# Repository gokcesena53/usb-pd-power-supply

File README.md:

# gopo — Masaüstü Güç Kaynağı

USB-C PD beslemeli, ESP32-C6 tabanlı, TFT ekranlı ve döner enkoderli
masaüstü ayarlanabilir güç kaynağı. Şematik ve PCB tasarımı KiCad ile yapılmıştır.

Depo yapısı [Open Hardware Template](https://github.com/mfhepp/open_hardware_template)
şablonunu izler.

## Klasör yapısı

| Klasör | İçerik |
| --- | --- |
| `hardware/` | KiCad projesi (`gopo.kicad_pro`, `.kicad_sch`, `.kicad_pcb`, `.kicad_dru`) ve kütüphane tabloları (`fp-lib-table`, `sym-lib-table`) |
| `hardware/libraries/` | Projeye özel sembol (`.kicad_sym`), footprint (`.pretty`) ve 3D model (`.3dshapes`) kütüphaneleri |
| `hardware/datasheets/` | Kullanılan bileşenlerin veri sayfaları |
| `hardware/docs/` | Ham ERC/DRC raporları, netlist'ler, doğrulama betikleri ve anlık görüntüler |
| `hardware/gerber/` | Üretim çıktıları (Gerber, drill) |
| `hardware/images/` | Şematik/PCB görüntüleri (PNG, SVG) |
| `hardware/pdf/` | Blok blok şematik PDF çıktıları ve inceleme belgeleri |
| `design_decisions/` | Tasarım kararları, hesaplamalar ve inceleme notları (Markdown) |
| `3d_design/` | Kutu/mekanik tasarım dosyaları |
| `software/` | Firmware, firmware gereksinimleri (`FIRMWARE_GEREKSINIMLERI.md`) ve yardımcı betikler |
| `backlog/` | Yapılacaklar ([Backlog.md](https://github.com/MrLesk/Backlog.md)); `backlog board` veya `backlog browser` ile görüntülenir |
| `docs/` | GitHub Pages proje sayfası |
| `.claude/skills/` | KiCad şema üretimi için Claude Code skill'i ve araçları |

## Şema araçları

`.claude/skills/kicad-schematic/` altında şema üretimi ve temizliği için
bir Claude Code skill'i ve iki bağımsız betik bulunur:

```bash
SK=.claude/skills/kicad-schematic/scripts
cd hardware
python3 ../$SK/render.py gopo.kicad_sch --list
python3 ../$SK/render.py gopo.kicad_sch --page 10 --crop 255 26 410 128 -o /tmp/r
python3 ../$SK/verify.py gopo.kicad_sch --show PD_VOUT V_PRE
```

`render.py` şemayı PNG'ye çevirir ve mm cinsinden bir bölgeye yakınlaşır;
`verify.py` ERC çalıştırıp netlist'i bir referansla karşılaştırır.
Gereksinimler: `kicad-cli`, `poppler-utils` (pdftoppm, pdftotext), Python 3.

Yöntem [American-Embedded/kistack](https://github.com/American-Embedded/kistack)
schematic skill'ine dayanır (MIT); kopyası ve lisansı skill'in `references/`
klasöründedir.

## Revizyonlar

Aktif revizyon **REV_B**'dir; `hardware/` klasöründeki tasarım budur.
Üretilmiş olan REV_A tasarımı depodan çıkarılmıştır ve yalnızca git geçmişinde
bulunur (`git log --diff-filter=D -- "masaüstü güç kaynağı.kicad_pcb"`).

Değişiklik kaydı için `CHANGES.TXT` dosyasına bakınız.

## Tasarım kuralları ve PCB üretimi

Tasarım kuralları `hardware/gopo.kicad_dru` dosyasındadır. Üretime göndermeden önce
seçtiğiniz üreticinin yeteneklerine uyduğunu doğrulayın.

PCB ipek baskısına ve şematiğe **"Licensed under CERN OHL v.1.2"** metnini
eklemeyi unutmayın.

## Lisans

Donanım tasarımı CERN OHL v.1.2 altında, `software/` klasöründeki yazılım MIT
lisansı altında dağıtılmaktadır. Ayrıntılar için `LICENSE` ve
`cern_ohl_v_1_2.txt` dosyalarına bakınız.

> **Not:** `LICENSE` dosyasındaki `<TELİF HAKKI SAHİBİ>` alanı henüz
> doldurulmamıştır; yayımlamadan önce doldurun veya farklı bir lisans seçin.

## Sorumluluk reddi

BU TASARIM VE YAZILIM, AÇIK VEYA ZIMNİ HİÇBİR GARANTİ OLMAKSIZIN "OLDUĞU GİBİ"
SAĞLANMAKTADIR. YAZARLAR VEYA TELİF HAKKI SAHİPLERİ, TASARIMIN VEYA YAZILIMIN
KULLANIMINDAN DOĞAN HİÇBİR TALEP, ZARAR VEYA SORUMLULUKTAN SORUMLU TUTULAMAZ.

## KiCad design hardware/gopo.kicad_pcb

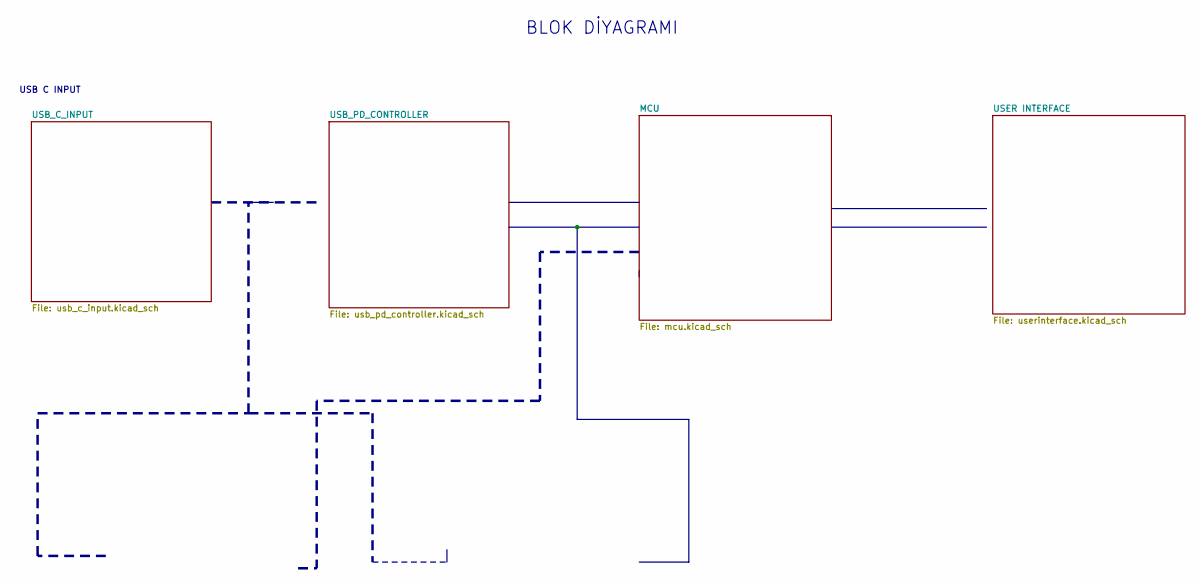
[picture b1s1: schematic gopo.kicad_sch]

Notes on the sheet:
USB C INPUT
BLOK DİYAGRAMI

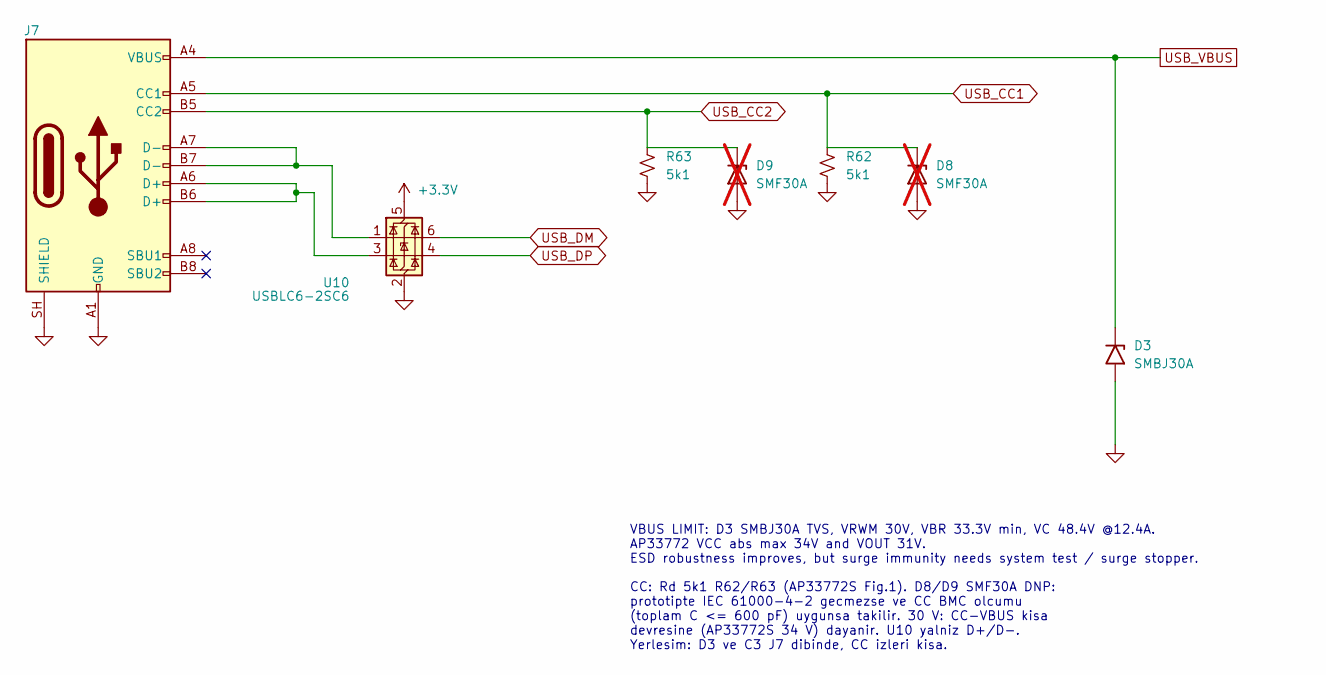
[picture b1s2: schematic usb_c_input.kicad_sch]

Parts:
D3: SMBJ30A; D_SMB; MPN SMBJ30A-E3/52
D8, D9: SMF30A; D_SOD-123F; MPN SMF30A-TKS; not fitted
J7: USB_C_Receptacle_USB2.0_16P; USB_C_Receptacle_GCT_USB4105-xx-A_16P_TopMnt_Horizontal; VoltageRating TBD; MPN USB4105-GF-A
R62, R63: 5k1; R_0402_1005Metric; Tolerance +/-1%; VoltageRating 50V; MPN HP02WAF5101TCE
U10: USBLC6-2SC6; SOT-23-6; MPN USBLC6-2SC6

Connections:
+3.3V: U10.5 (VBUS); also elsewhere on the board
GND: D3.2 (A2), D8.2 (A), D9.2 (A), J7.A1 (GND), J7.A12 (GND), J7.B1 (GND), J7.B12 (GND), J7.SH (SHIELD), R62.2, R63.2, U10.2 (GND); also elsewhere on the board
USB_CC1: D8.1 (K), J7.A5 (CC1), R62.1; also elsewhere on the board
USB_CC2: D9.1 (K), J7.B5 (CC2), R63.1; also elsewhere on the board
USB_VBUS: D3.1 (A1), J7.A4 (VBUS), J7.A9 (VBUS), J7.B4 (VBUS), J7.B9 (VBUS); also elsewhere on the board

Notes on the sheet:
VBUS LIMIT: D3 SMBJ30A TVS, VRWM 30V, VBR 33.3V min, VC 48.4V @12.4A. AP33772 VCC abs max 34V and VOUT 31V. ESD robustness improves, but surge immunity needs system test / surge stopper.
CC: Rd 5k1 R62/R63 (AP33772S Fig.1). D8/D9 SMF30A DNP: prototipte IEC 61000-4-2 gecmezse ve CC BMC olcumu (toplam C <= 600 pF) uygunsa takilir. 30 V: CC-VBUS kisa devresine (AP33772S 34 V) dayanir. U10 yalniz D+/D-. Yerlesim: D3 ve C3 J7 dibinde, CC izleri kisa.

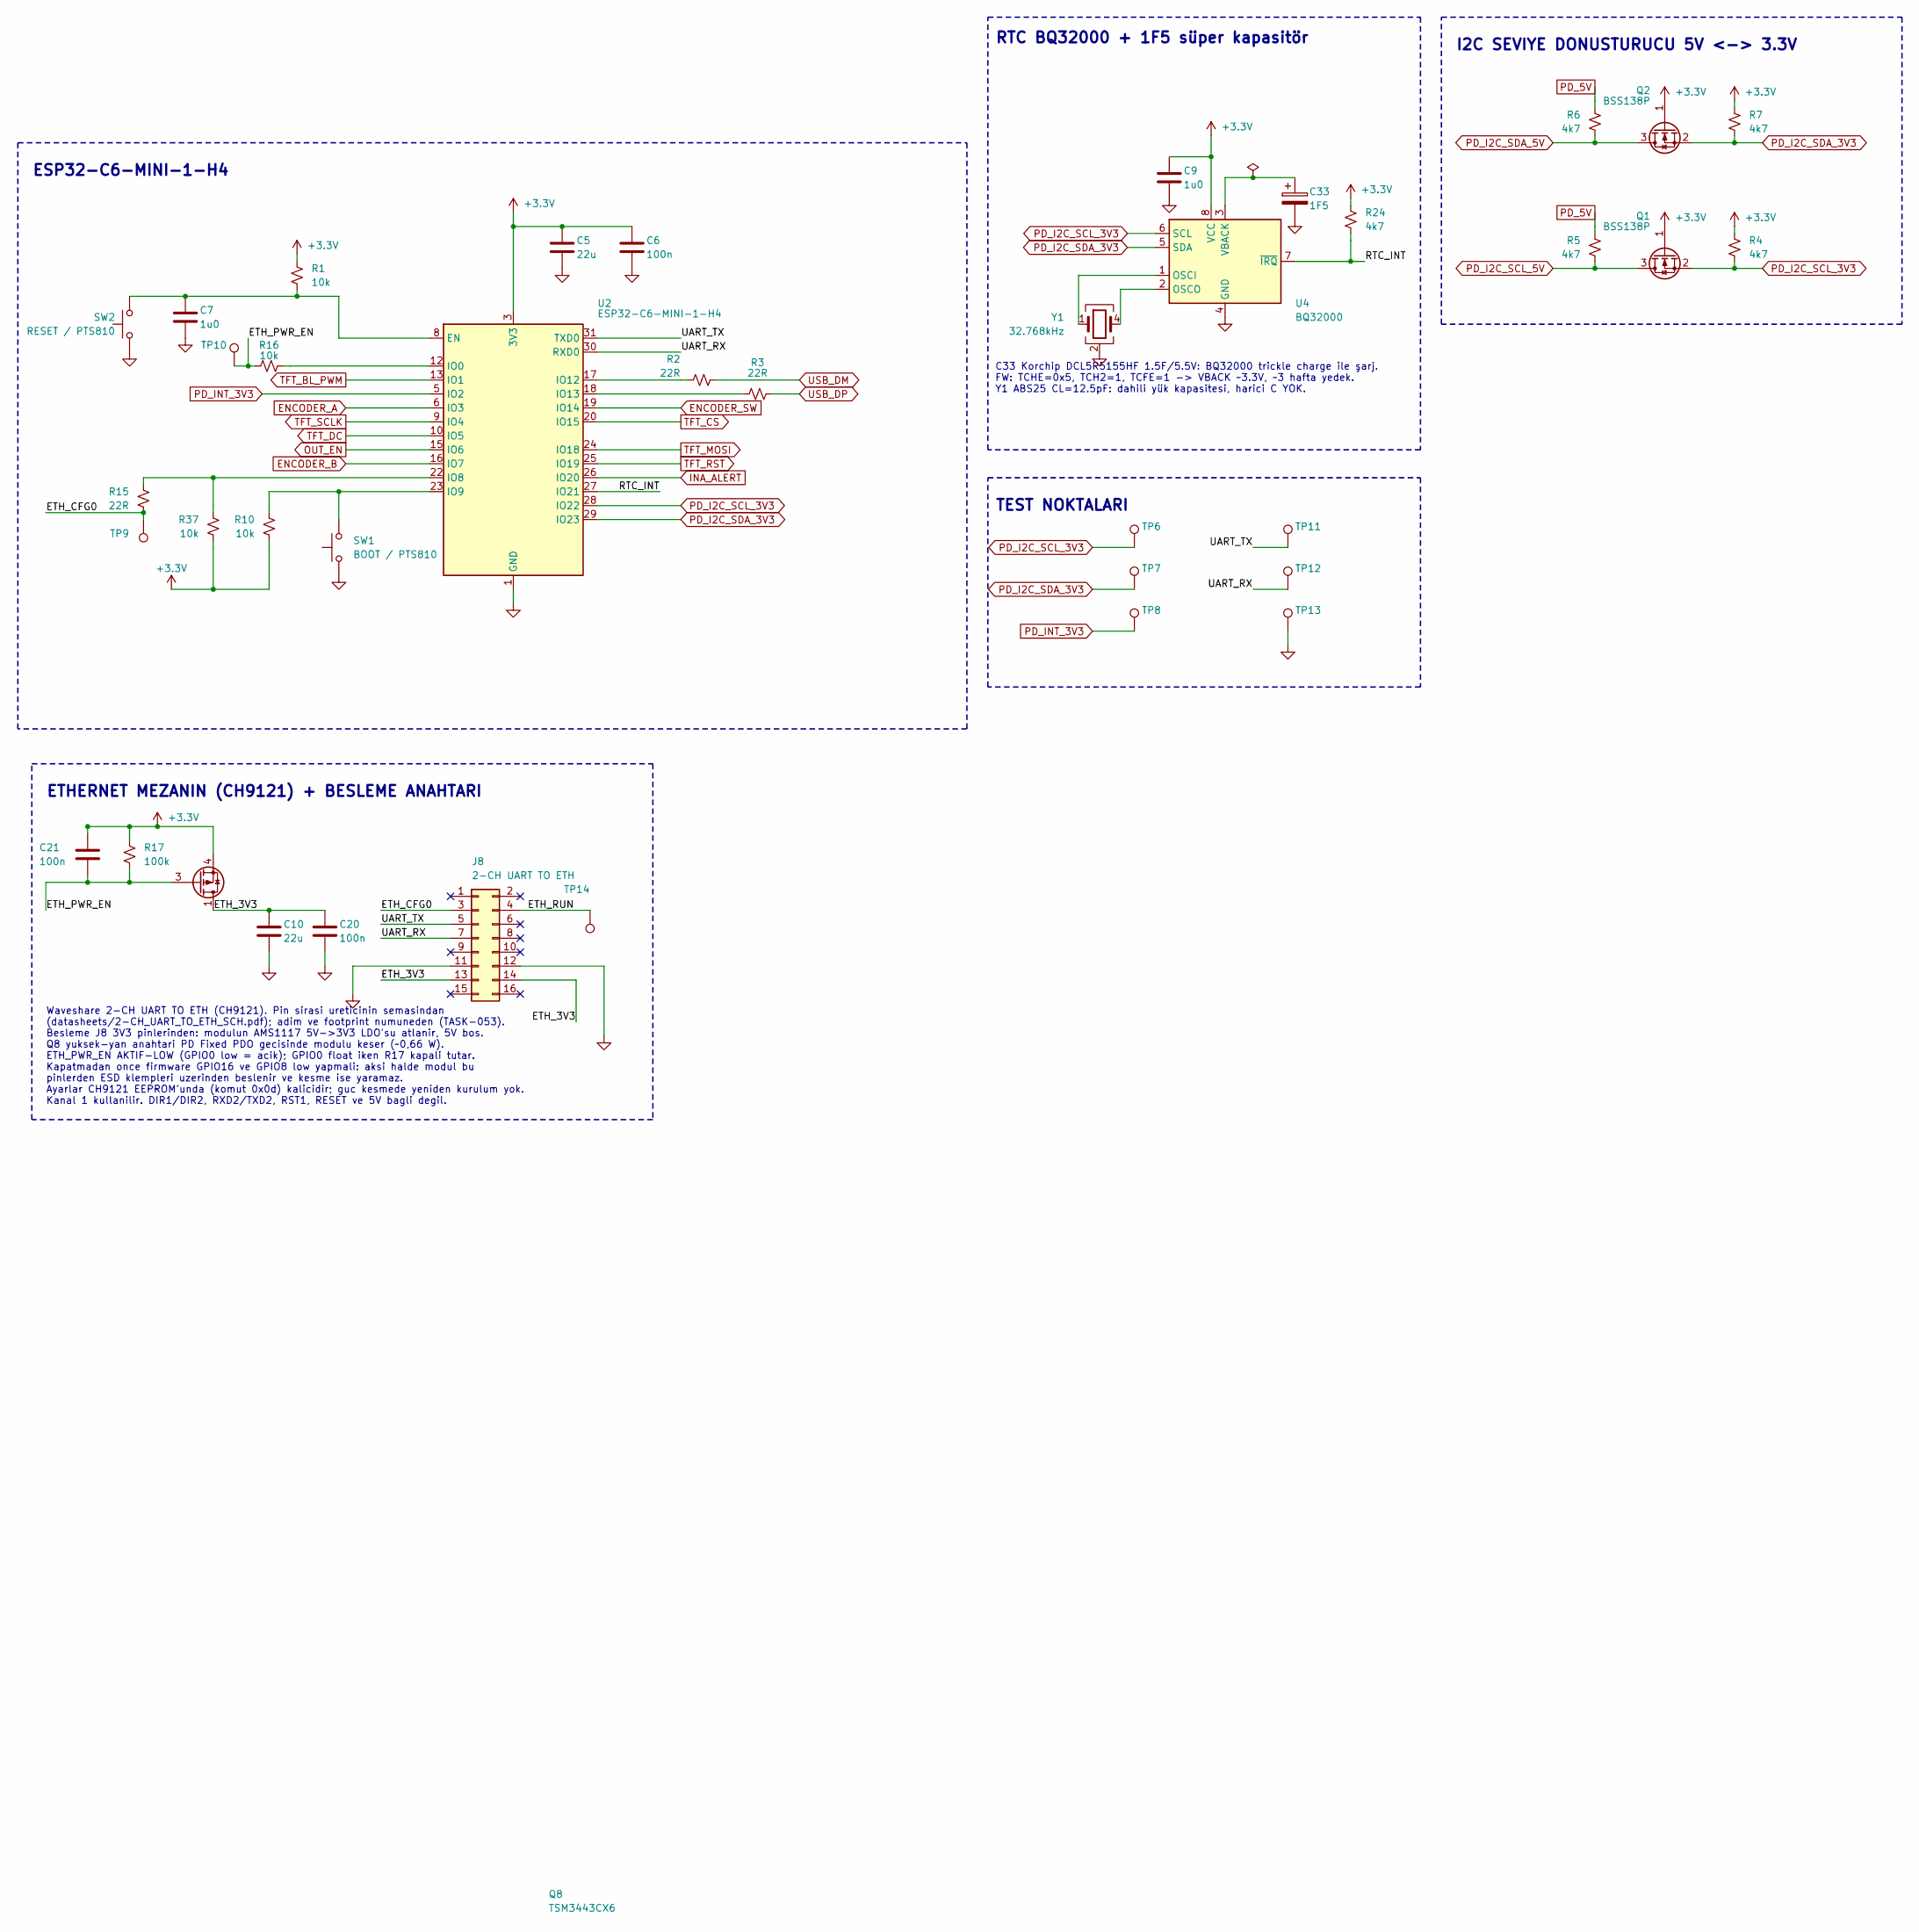
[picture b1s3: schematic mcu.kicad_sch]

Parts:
C5, C10: 22u; C_0805_2012Metric; Tolerance +/-20%; VoltageRating 10V; MPN GRT21BC81A226ME13K
C6, C20, C21: 100n; C_0402_1005Metric; Tolerance +/-10%; VoltageRating 50V; MPN CC0402KRX7R9BB104
C7, C9: 1u0; C_0402_1005Metric; Tolerance +/-10%; VoltageRating 16V; MPN EMK105BJ105KVHF
C33: 1F5; Korchip_DCL_H-Type_D19.0mm_P20.00mm_Horizontal; VoltageRating 5.5V; Tolerance -20%/+80%; MPN DCL5R5155HF
J8: 2-CH UART TO ETH; Waveshare_2-CH_UART_TO_ETH; VoltageRating TBD; MPN TBD
Q1, Q2: BSS138P; SOT-23; VoltageDS 60V; MPN BSS138P,215
Q8: TSM3443CX6; SOT-23-6; MPN TSM3443CX6 RF
R1, R10, R37: 10k; R_0402_1005Metric; Tolerance +/-0.1%; VoltageRating 25V; MPN TC0250B1002TCC
R2, R3, R15: 22R; R_0402_1005Metric; Tolerance +/-1%; VoltageRating 50V; MPN RC0402FR-0722RP
R4, R5, R6, R7, R24: 4k7; R_0402_1005Metric; Tolerance +/-1%; VoltageRating 50V; MPN HP02WAF4701TCE
R16: 10k; R_0402_1005Metric; Tolerance +/-1%; VoltageRating 50V; MPN TC0250B1002TCC
R17: 100k; R_0402_1005Metric; Tolerance +/-1%; VoltageRating 50V; MPN 0402WGF1003TCE
SW1: BOOT / PTS810; SW_SPST_PTS810; MPN PTS810 SJS 250 SMTR LFS
SW2: RESET / PTS810; SW_SPST_PTS810; MPN PTS810 SJS 250 SMTR LFS
TP6, TP7, TP8, TP9, TP10, TP11, TP12, TP13, TP14: TestPoint; TestPoint_Pad_D1.0mm; MPN N/A
U2: ESP32-C6-MINI-1-H4; ESP32-C6-MINI-1; MPN ESP32-C6-MINI-1-H4
U4: BQ32000; SOIC-8_3.9x4.9mm_P1.27mm; MPN BQ32000DR
Y1: 32.768kHz; Crystal_SMD_Abracon_ABS25-4Pin_8.0x3.8mm; MPN ABS25-32.768KHZ-T

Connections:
+3.3V: C5.1, C6.1, C9.1, C21.1, Q1.1 (G), Q2.1 (G), Q8.4 (S), R1.1, R4.2, R7.1, R10.2, R17.1, R24.1, R37.2, U2.3 (3V3), U4.8 (VCC); also elsewhere on the board
/MCU/ETH_3V3: C10.1, C20.1, J8.13, J8.14, Q8.1 (D), Q8.2 (D), Q8.5 (D), Q8.6 (D)
/MCU/ETH_CFG0: J8.3, R15.2, TP9.1 (1_1)
/MCU/ETH_PWR_EN: C21.2, Q8.3 (G), R16.1, R17.2, TP10.1 (1_1)
/MCU/ETH_RUN: J8.4, TP14.1
/MCU/RTC_INT: R24.2, U2.27 (IO21), U4.7 (~IRQ)
/MCU/UART_RX: J8.7, TP12.1, U2.30 (RXD0)
/MCU/UART_TX: J8.5, TP11.1, U2.31 (TXD0)
ENCODER_A: U2.6 (IO3); also elsewhere on the board
ENCODER_B: U2.16 (IO7); also elsewhere on the board
ENCODER_SW: U2.19 (IO14); also elsewhere on the board
GND: C5.2, C6.2, C7.1, C9.2, C10.2, C20.2, C33.2, J8.11, J8.12, SW1.1, SW2.1, TP13.1, U2.1 (GND), U2.2 (GND), U2.11 (GND), U2.14 (GND), U2.36 (GND), U2.37 (GND), U2.38 (GND), U2.39 (GND), U2.40 (GND), U2.41 (GND), U2.42 (GND), U2.43 (GND), U2.44 (GND), U2.45 (GND), U2.46 (GND), U2.47 (GND), U2.48 (GND), U2.49 (GND), U2.50 (GND), U2.51 (GND), U2.52 (GND), U2.53 (GND), U4.4 (GND), Y1.2 (G), Y1.3 (G); also elsewhere on the board
INA_ALERT: U2.26 (IO20); also elsewhere on the board
unnamed: C7.2, R1.2, SW2.2, U2.8 (EN)
unnamed: R16.2, U2.12 (IO0)
unnamed: R15.1, R37.1, U2.22 (IO8)
unnamed: R10.1, SW1.2, U2.23 (IO9)
unnamed: R2.1, U2.17 (IO12)
unnamed: R3.1, U2.18 (IO13)
unnamed: U4.1 (OSCI), Y1.1
unnamed: U4.2 (OSCO), Y1.4
unnamed: C33.1, U4.3 (VBACK)
OUT_EN: U2.15 (IO6); also elsewhere on the board
PD_5V: R5.1, R6.1; also elsewhere on the board
PD_I2C_SCL_3V3: Q1.2 (S), R4.1, TP6.1 (1_1), U2.28 (IO22), U4.6 (SCL); also elsewhere on the board
PD_I2C_SCL_5V: Q1.3 (D), R5.2; also elsewhere on the board
PD_I2C_SDA_3V3: Q2.2 (S), R7.2, TP7.1 (1_1), U2.29 (IO23), U4.5 (SDA); also elsewhere on the board
PD_I2C_SDA_5V: Q2.3 (D), R6.2; also elsewhere on the board
PD_INT_3V3: TP8.1 (1_1), U2.5 (IO2); also elsewhere on the board
TFT_BL_PWM: U2.13 (IO1); also elsewhere on the board
TFT_CS: U2.20 (IO15); also elsewhere on the board
TFT_DC: U2.10 (IO5); also elsewhere on the board
TFT_MOSI: U2.24 (IO18); also elsewhere on the board
TFT_RST: U2.25 (IO19); also elsewhere on the board
TFT_SCLK: U2.9 (IO4); also elsewhere on the board

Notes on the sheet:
TEST NOKTALARI
RTC BQ32000 + 1F5 süper kapasitör
C33 Korchip DCL5R5155HF 1.5F/5.5V: BQ32000 trickle charge ile şarj. FW: TCHE=0x5, TCH2=1, TCFE=1 -> VBACK ~3.3V, ~3 hafta yedek. Y1 ABS25 CL=12.5pF: dahili yük kapasitesi, harici C YOK.
ESP32-C6-MINI-1-H4
I2C SEVIYE DONUSTURUCU 5V <-> 3.3V
ETHERNET MEZANIN (CH9121) + BESLEME ANAHTARI
Waveshare 2-CH UART TO ETH (CH9121). Pin sirasi ureticinin semasindan (datasheets/2-CH_UART_TO_ETH_SCH.pdf); adim ve footprint numuneden (TASK-053). Besleme J8 3V3 pinlerinden: modulun AMS1117 5V->3V3 LDO'su atlanir, 5V bos. Q8 yuksek-yan anahtari PD Fixed PDO gecisinde modulu keser (~0,66 W). ETH_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

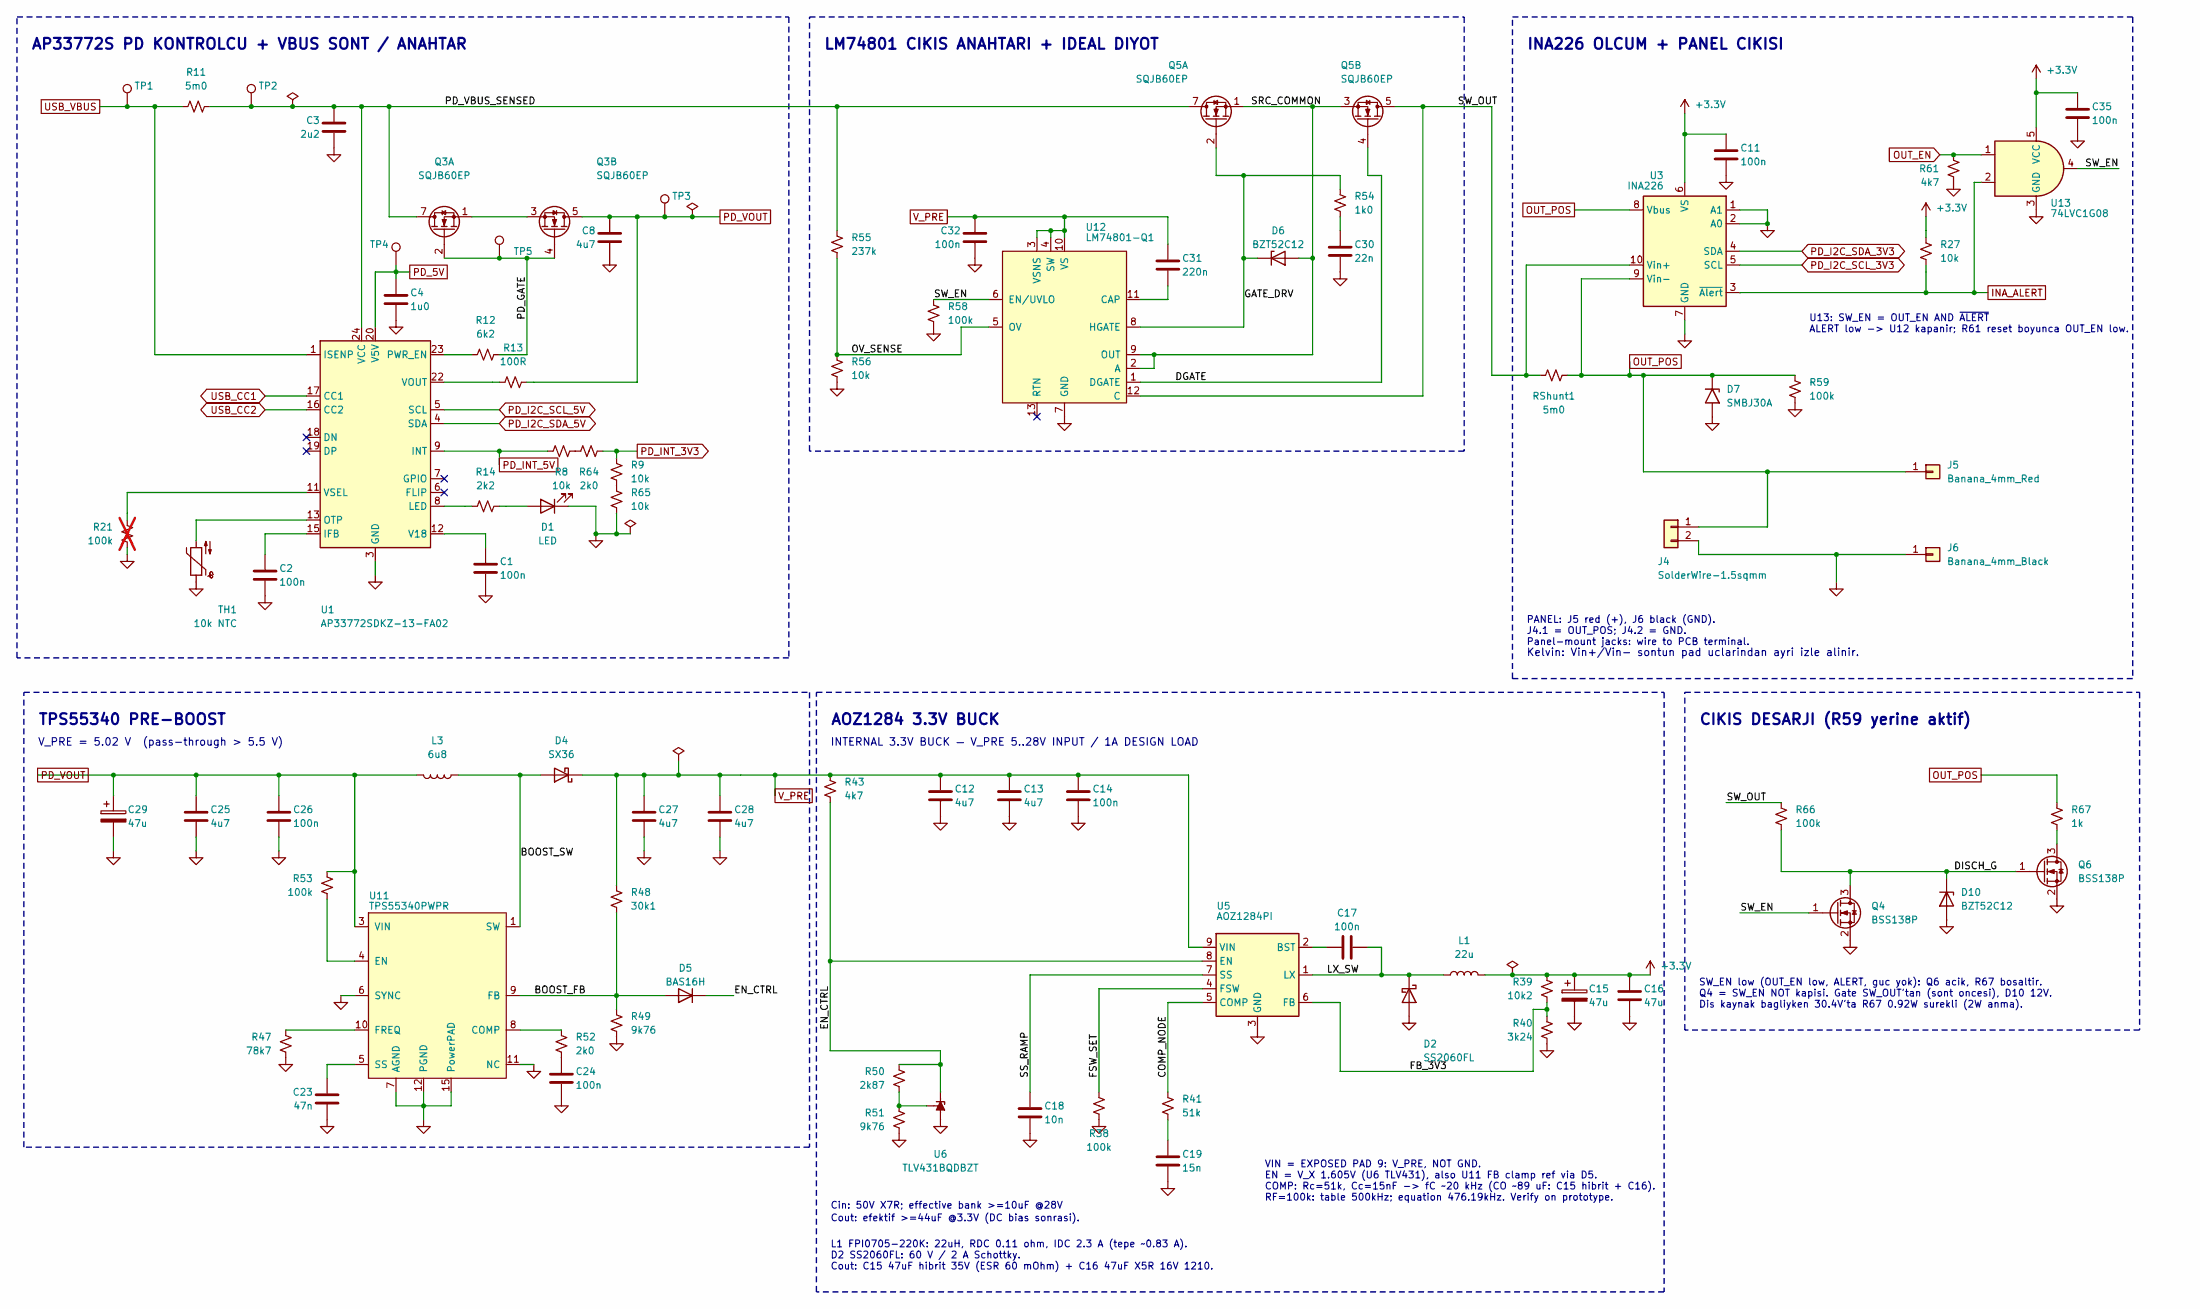
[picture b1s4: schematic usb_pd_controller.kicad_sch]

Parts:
C1, C2, C11, C14, C17, C24, C26, C32, C35: 100n; C_0402_1005Metric; Tolerance +/-10%; VoltageRating 50V; MPN CC0402KRX7R9BB104
C3: 2u2; C_0805_2012Metric; Tolerance +/-10%; VoltageRating 50V; MPN CL21A225KB9LNNC
C4: 1u0; C_0402_1005Metric; Tolerance +/-10%; VoltageRating 16V; MPN EMK105BJ105KVHF
C8, C12, C13, C25, C27, C28: 4u7; C_1210_3225Metric; Tolerance +/-10%; VoltageRating 50V; MPN CL32B475KBJNNNE
C15, C29: 47u; CP_Elec_6.3x5.8; VoltageRating 35V; Tolerance +/-20%; MPN EEHZA1V470P
C16: 47u; C_1210_3225Metric; Tolerance +/-10%; VoltageRating 16V; MPN CL32A476KOJNNNE
C18: 10n; C_0402_1005Metric; Tolerance +/-10%; VoltageRating 25V; MPN CL05B103KA5NNNC
C19: 15n; C_0402_1005Metric; Tolerance +/-10%; VoltageRating 16V; MPN CL05B153KO5NNNC
C23: 47n; C_0402_1005Metric; Tolerance +/-10%; VoltageRating 16V; MPN CL05B473KO5NNNC
C30: 22n; C_0402_1005Metric; Tolerance +/-10%; VoltageRating 50V; MPN CC0402KRX7R9BB223
C31: 220n; C_0603_1608Metric; Tolerance +/-10%; VoltageRating 25V; MPN CL10B224KA8NNNC
D1: LED; LED_0402_1005Metric; MPN APHHS1005SURCK
D2: SS2060FL; D_SOD-123F; MPN SS2060FL_R1_00001
D4: SX36; D_SMA; MPN SX36_R1_00001
D5: BAS16H; D_SOD-323; MPN BAS16HT1G
D6, D10: BZT52C12; D_SOD-123; MPN BZT52-C12_R1_00001
D7: SMBJ30A; D_SMB; MPN SMBJ30A-E3/52
J4: SolderWire-1.5sqmm; SolderWire-1.5sqmm_1x02_P7.8mm_D1.7mm_OD3.9mm; VoltageRating TBD; MPN N/A (PCB pedi)
J5: Banana_4mm_Red; Cinch_108-0902-001_Panel; VoltageRating TBD; MPN KOM.KNN.06.000021
J6: Banana_4mm_Black; Cinch_108-0903-001_Panel; VoltageRating TBD; MPN KOM.KNN.06.000022
L1: 22u; L_CoreMaster_FPI0705_7.8x7.0mm_H5.0; Tolerance TBD; MPN FPI0705-220K
L3: 6u8; L_7.3x7.3_H4.5; Tolerance TBD; MPN SRI0704-6R8M
Q3, Q5: SQJB60EP; Vishay_PowerPAK_SO-8L_Dual; VoltageDS 60V; MPN SQJB60EP-T1_GE3
Q4, Q6: BSS138P; SOT-23; VoltageDS 60V; MPN BSS138P,215
R8, R9, R27, R56, R65: 10k; R_0402_1005Metric; Tolerance +/-0.1%; VoltageRating 25V; MPN TC0250B1002TCC
R11: 5m0; R_2512_6332Metric; Tolerance +/-1%; VoltageRating N/A; MPN BVT-I-R005-1.0
R12: 6k2; R_0402_1005Metric; Tolerance +/-1%; VoltageRating 50V; MPN 0402WGF6201TCE
R13: 100R; R_0402_1005Metric; Tolerance +/-0.1%; VoltageRating 25V; MPN TC0250B1000TCC
R14: 2k2; R_0402_1005Metric; Tolerance +/-1%; VoltageRating 50V; MPN ERJ2RKF2201X
R21: 100k; R_0402_1005Metric; Tolerance +/-1%; VoltageRating 50V; MPN CQ02WGF1003TCE; not fitted
R38, R53, R58: 100k; R_0402_1005Metric; Tolerance +/-1%; VoltageRating 50V; MPN CQ02WGF1003TCE
R39: 10k2; R_0402_1005Metric; Tolerance +/-1%; VoltageRating 50V; MPN RC1005F1022CS
R40: 3k24; R_0402_1005Metric; Tolerance +/-1%; VoltageRating 50V; MPN ERJ2RKF3241X
R41: 51k; R_0402_1005Metric; Tolerance +/-1%; VoltageRating 50V; MPN 0402WGF5102TCE
R43: 4k7; R_2512_6332Metric; Tolerance +/-1%; VoltageRating 200V; MPN CQ121WF4701T4E
R47: 78k7; R_0402_1005Metric; Tolerance +/-1%; VoltageRating 50V; MPN 0402WGF7872TCE
R48: 30k1; R_0402_1005Metric; Tolerance +/-1%; VoltageRating 50V; MPN 0402WGF3012TCE
R49, R51: 9k76; R_0402_1005Metric; Tolerance +/-1%; VoltageRating 50V; MPN 0402WGF9761TCE
R50: 2k87; R_0402_1005Metric; Tolerance +/-1%; VoltageRating 50V; MPN 0402WGF2871TCE
R52, R64: 2k0; R_0402_1005Metric; Tolerance +/-1%; VoltageRating 50V; MPN ERJ2RKF2001X
R54: 1k0; R_0402_1005Metric; Tolerance +/-0.1%; VoltageRating 50V; MPN RT0402BRD071KL
R55: 237k; R_0402_1005Metric; Tolerance +/-1%; VoltageRating 50V; MPN 0402WGF2373TCE
R59, R66: 100k; R_0603_1608Metric; Tolerance +/-1%; VoltageRating 75V; MPN CRCW0603100KFKTBBC
R61: 4k7; R_0402_1005Metric; Tolerance +/-1%; VoltageRating 50V; MPN HP02WAF4701TCE
R67: 1k; R_2512_6332Metric; Tolerance +/-1%; VoltageRating 500V; MPN PS122WF1001T4E
RShunt1: 5m0; R_2512_6332Metric; Tolerance +/-1%; VoltageRating N/A; MPN BVT-I-R005-1.0
TH1: 10k NTC; R_0402_1005Metric; MPN TSM0B103F3381RZ
TP1, TP2, TP3, TP4, TP5: TestPoint; TestPoint_Pad_D1.0mm; MPN N/A
U1: AP33772SDKZ-13-FA02; Texas_RTW_WQFN-24-1EP_4x4mm_P0.5mm_EP2.7x2.7mm; MPN AP33772SDKZ-13-FA02
U3: INA226; TSSOP-10_3x3mm_P0.5mm; MPN INA226AIDGSR
U5: AOZ1284PI; SOIC-8-1EP_3.9x4.9mm_P1.27mm_EP2.71x3.7mm; MPN AOZ1284PI
U6: TLV431BQDBZT; SOT-23; MPN TLV431BQDBZT
U11: TPS55340PWPR; Texas_HTSSOP-14-1EP_4.4x5mm_P0.65mm_EP3.4x5mm_Mask3.155x3.2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; MPN TPS55340PWPR
U12: LM74801-Q1; WSON-12-1EP_3x3mm_P0.5mm_EP1.5x2.5mm; MPN LM74801QDRRRQ1
U13: 74LVC1G08; SOT-23-5; MPN SN74LVC1G08DBVR

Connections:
+3.3V: C11.1, C15.1, C16.1, C35.1, L1.2, R27.1, R39.1, U3.6 (VS), U13.5 (VCC); also elsewhere on the board
/USB_PD_CONTROLLER/BOOST_FB: D5.2 (A), R48.2, R49.1, U11.9 (FB)
/USB_PD_CONTROLLER/BOOST_SW: D4.2 (A), L3.1, U11.1 (SW), U11.2 (SW)
/USB_PD_CONTROLLER/COMP_NODE: R41.1, U5.5 (COMP)
/USB_PD_CONTROLLER/DGATE: Q5.4 (G), U12.1 (DGATE)
/USB_PD_CONTROLLER/DISCH_G: D10.1 (K), Q4.3 (D), Q6.1 (G), R66.2
/USB_PD_CONTROLLER/EN_CTRL: D5.1 (K), R43.2, R50.1, U5.8 (EN), U6.2 (REF)
/USB_PD_CONTROLLER/FB_3V3: R39.2, R40.1, U5.6 (FB)
/USB_PD_CONTROLLER/FSW_SET: R38.1, U5.4 (FSW)
/USB_PD_CONTROLLER/GATE_DRV: D6.1 (K), Q5.2 (G), R54.1, U12.8 (HGATE)
/USB_PD_CONTROLLER/LX_SW: C17.2, D2.1 (K), L1.1, U5.1 (LX)
/USB_PD_CONTROLLER/OV_SENSE: R55.2, R56.1, U12.5 (OV)
/USB_PD_CONTROLLER/PD_GATE: Q3.2 (G), Q3.4 (G), R12.2, TP5.1 (1_1)
/USB_PD_CONTROLLER/PD_VBUS_SENSED: C3.1, Q3.7 (D), Q3.8 (D), Q5.7 (D), Q5.8 (D), R11.2, R55.1, TP2.1 (1_1), U1.24 (VCC)
/USB_PD_CONTROLLER/SRC_COMMON: D6.2 (A), Q5.1 (S), Q5.3 (S), U12.2 (A), U12.9 (OUT)
/USB_PD_CONTROLLER/SS_RAMP: C18.1, U5.7 (SS)
/USB_PD_CONTROLLER/SW_EN: Q4.1 (G), R58.1, U12.6 (EN/UVLO), U13.4
/USB_PD_CONTROLLER/SW_OUT: Q5.5 (D), Q5.6 (D), R66.1, RShunt1.1, U3.10 (Vin+), U12.12 (C)
GND: C1.2, C2.2, C3.2, C4.2, C8.2, C11.2, C12.2, C13.2, C14.2, C15.2, C16.2, C18.2, C19.2, C23.2, C24.2, C25.2, C26.2, C27.2, C28.2, C29.2, C30.2, C32.2, C35.2, D1.1 (K), D2.2 (A), D7.2 (A2), D10.2 (A), J4.2, J6.1, Q4.2 (S), Q6.2 (S), R21.1, R38.2, R40.2, R47.2, R49.2, R51.2, R56.2, R58.2, R59.2, R61.2, R65.2, TH1.1, U1.3 (GND), U1.25 (GND), U3.1 (A1), U3.2 (A0), U3.7 (GND), U5.3 (GND), U6.3 (A), U11.6 (SYNC), U11.7 (AGND), U11.11 (NC), U11.12 (PGND), U11.13 (PGND), U11.14 (PGND), U11.15 (PowerPAD), U12.7 (GND), U13.3 (GND); also elsewhere on the board
INA_ALERT: R27.2, U3.3 (~Alert), U13.2; also elsewhere on the board
unnamed: C19.1, R41.2
unnamed: C24.1, R52.2
unnamed: C30.1, R54.2
unnamed: D1.2 (A), R14.2
unnamed: Q3.1 (S), Q3.3 (S)
unnamed: Q6.3 (D), R67.2
unnamed: R8.2, R64.1
unnamed: R9.2, R65.1
unnamed: C2.1, U1.15 (IFB)
unnamed: R14.1, U1.8 (LED)
unnamed: TH1.2, U1.13 (OTP)
unnamed: R12.1, U1.23 (PWR_EN)
unnamed: C1.1, U1.12 (V18)
unnamed: R13.1, U1.22 (VOUT)
unnamed: R21.2, U1.11 (VSEL)
unnamed: C17.1, U5.2 (BST)
unnamed: R50.2, R51.1, U6.1 (K)
unnamed: R52.1, U11.8 (COMP)
unnamed: R53.2, U11.4 (EN)
unnamed: R47.1, U11.10 (FREQ)
unnamed: C23.1, U11.5 (SS)
unnamed: C31.2, U12.11 (CAP)
OUT_EN: R61.1, U13.1; also elsewhere on the board
OUT_POS: D7.1 (A1), J4.1, J5.1, R59.1, R67.1, RShunt1.2, U3.8 (Vbus), U3.9 (Vin-)
PD_5V: C4.1, TP4.1 (1_1), U1.20 (V5V); also elsewhere on the board
PD_I2C_SCL_3V3: U3.5 (SCL); also elsewhere on the board
PD_I2C_SCL_5V: U1.5 (SCL); also elsewhere on the board
PD_I2C_SDA_3V3: U3.4 (SDA); also elsewhere on the board
PD_I2C_SDA_5V: U1.4 (SDA); also elsewhere on the board
PD_INT_3V3: R9.1, R64.2; also elsewhere on the board
PD_INT_5V: R8.1, U1.9 (INT)
PD_VOUT: C8.1, C25.1, C26.1, C29.1, L3.2, Q3.5 (D), Q3.6 (D), R13.2, R53.1, TP3.1 (1_1), U11.3 (VIN)
USB_CC1: U1.17 (CC1); also elsewhere on the board
USB_CC2: U1.16 (CC2); also elsewhere on the board
USB_VBUS: R11.1, TP1.1 (1_1), U1.1 (ISENP); also elsewhere on the board
V_PRE: C12.1, C13.1, C14.1, C27.1, C28.1, C31.1, C32.1, D4.1 (K), R43.1, R48.1, U5.9 (VIN), U12.3 (VSNS), U12.4 (SW), U12.10 (VS)

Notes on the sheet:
V_PRE = 5.02 V (pass-through > 5.5 V)
AP33772S PD KONTROLCU + VBUS SONT / ANAHTAR
TPS55340 PRE-BOOST
Kelvin: Vin+/Vin- sontun pad uclarindan ayri izle alinir.
Cin: 50V X7R; effective bank >=10uF @28V
AOZ1284 3.3V BUCK
INA226 OLCUM + PANEL CIKISI
PANEL: J5 red (+), J6 black (GND). J4.1 = OUT_POS; J4.2 = GND. Panel-mount jacks: wire to PCB terminal.
U13: SW_EN = OUT_EN AND ~{ALERT} ALERT low -> U12 kapanir; R61 reset boyunca OUT_EN low.
LM74801 CIKIS ANAHTARI + IDEAL DIYOT
VIN = EXPOSED PAD 9: V_PRE, NOT GND. EN = V_X 1.605V (U6 TLV431), also U11 FB clamp ref via D5. COMP: Rc=51k, Cc=15nF -> fC ~20 kHz (CO ~89 uF: C15 hibrit + C16). RF=100k: table 500kHz; equation 476.19kHz. Verify on prototype.
INTERNAL 3.3V BUCK — V_PRE 5..28V INPUT / 1A DESIGN LOAD
Cout: efektif >=44uF @3.3V (DC bias sonrasi).
L1 FPI0705-220K: 22uH, RDC 0.11 ohm, IDC 2.3 A (tepe ~0.83 A). D2 SS2060FL: 60 V / 2 A Schottky. Cout: C15 47uF hibrit 35V (ESR 60 mOhm) + C16 47uF X5R 16V 1210.
CIKIS DESARJI (R59 yerine aktif)
SW_EN low (OUT_EN low, ALERT, guc yok): Q6 acik, R67 bosaltir. Q4 = SW_EN NOT kapisi. Gate SW_OUT'tan (sont oncesi), D10 12V. Dis kaynak bagliyken 30.4V'ta R67 0.92W surekli (2W anma).

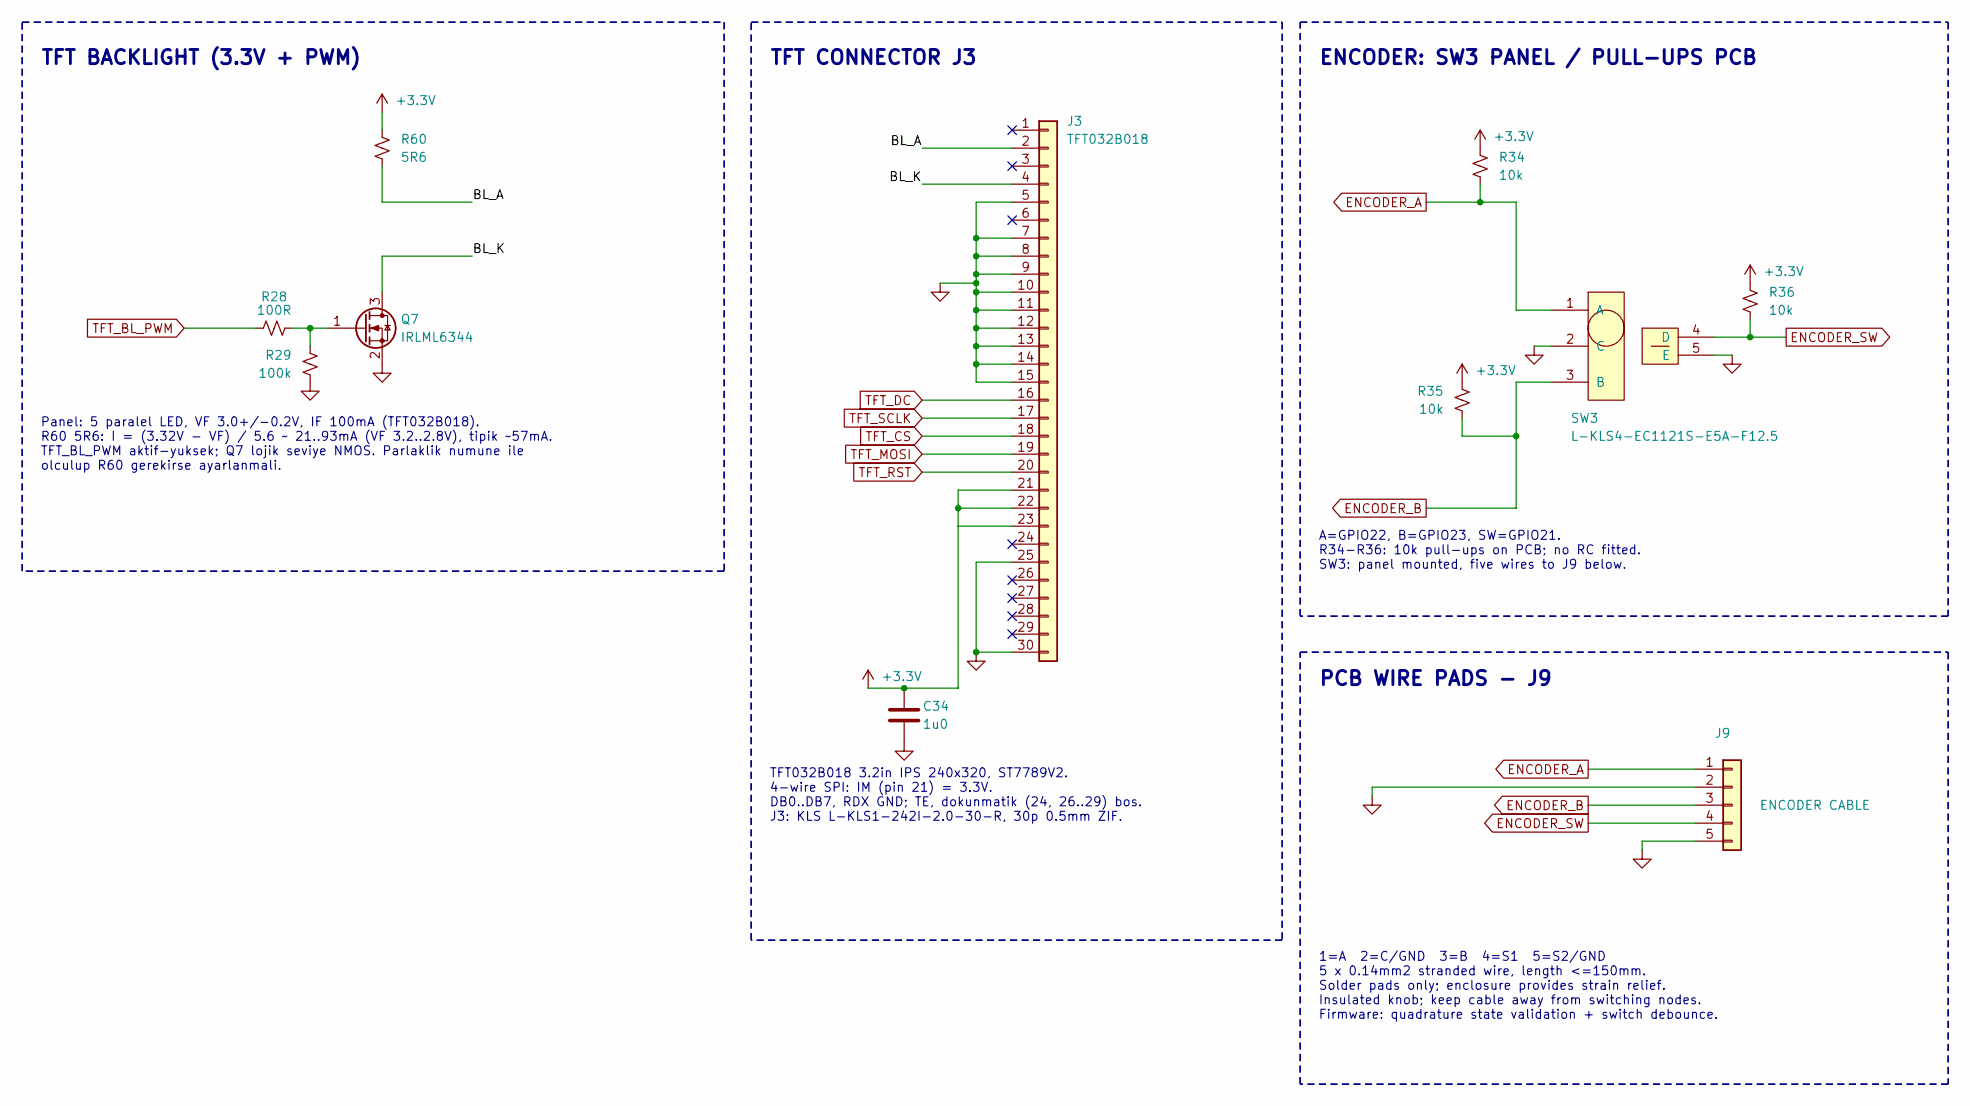
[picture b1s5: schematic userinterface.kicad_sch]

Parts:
C34: 1u0; C_0402_1005Metric; Tolerance +/-10%; VoltageRating 16V; MPN EMK105BJ105KVHF
J3: TFT032B018; KLS_L-KLS1-242I-2.0-30_1x30-2MP_P0.50mm_Horizontal; VoltageRating 50V; MPN L-KLS1-242I-2.0-30-R
J9: ENCODER CABLE; SolderWire-0.25sqmm_1x05_P4.2mm_D0.65mm_OD1.7mm; MPN N/A - PCB solder pads
Q7: IRLML6344; SOT-23; VoltageDS 30V; MPN IRLML6344TRPBF
R28: 100R; R_0402_1005Metric; Tolerance +/-0.1%; VoltageRating 25V; MPN TC0250B1000TCC
R29: 100k; R_0402_1005Metric; Tolerance +/-1%; VoltageRating 50V; MPN CQ02WGF1003TCE
R34, R35, R36: 10k; R_0402_1005Metric; Tolerance +/-0.1%; VoltageRating 25V; MPN TC0250B1002TCC
R60: 5R6; R_0805_2012Metric; Tolerance +/-5%; VoltageRating 150V; MPN CRT05J7F5R60
SW3: L-KLS4-EC1121S-E5A-F12.5; MPN L-KLS4-EC1121S-E5A-F12.5

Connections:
+3.3V: C34.1, J3.21, J3.22, J3.23, R34.1, R35.1, R36.1, R60.1; also elsewhere on the board
/USER INTERFACE/BL_A: J3.2, R60.2
/USER INTERFACE/BL_K: J3.4, Q7.3 (D)
ENCODER_A: J9.1, R34.2, SW3.1 (A); also elsewhere on the board
ENCODER_B: J9.3, R35.2, SW3.3 (B); also elsewhere on the board
ENCODER_SW: J9.4, R36.2, SW3.4 (D); also elsewhere on the board
GND: C34.2, J3.5, J3.7, J3.8, J3.9, J3.10, J3.11, J3.12, J3.13, J3.14, J3.15, J3.25, J3.30, J9.2, J9.5, Q7.2 (S), R29.2, SW3.2 (C), SW3.5 (E); also elsewhere on the board
unnamed: Q7.1 (G), R28.2, R29.1
TFT_BL_PWM: R28.1; also elsewhere on the board
TFT_CS: J3.18; also elsewhere on the board
TFT_DC: J3.16; also elsewhere on the board
TFT_MOSI: J3.19; also elsewhere on the board
TFT_RST: J3.20; also elsewhere on the board
TFT_SCLK: J3.17; also elsewhere on the board

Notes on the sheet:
TFT CONNECTOR J3
TFT BACKLIGHT (3.3V + PWM)
Panel: 5 paralel LED, VF 3.0+/-0.2V, IF 100mA (TFT032B018). R60 5R6: I = (3.32V - VF) / 5.6 ~ 21..93mA (VF 3.2..2.8V), tipik ~57mA. TFT_BL_PWM aktif-yuksek; Q7 lojik seviye NMOS. Parlaklik numune ile olculup R60 gerekirse ayarlanmali.
TFT032B018 3.2in IPS 240x320, ST7789V2. 4-wire SPI: IM (pin 21) = 3.3V. DB0..DB7, RDX GND; TE, dokunmatik (24, 26..29) bos. J3: KLS L-KLS1-242I-2.0-30-R, 30p 0.5mm ZIF.
ENCODER: SW3 PANEL / PULL-UPS PCB
A=GPIO22, B=GPIO23, SW=GPIO21. R34-R36: 10k pull-ups on PCB; no RC fitted. SW3: panel mounted, five wires to J9 below.
PCB WIRE PADS - J9
1=A 2=C/GND 3=B 4=S1 5=S2/GND 5 x 0.14mm2 stranded wire, length <=150mm. Solder pads only; enclosure provides strain relief. Insulated knob; keep cable away from switching nodes. Firmware: quadrature state validation + switch debounce.

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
